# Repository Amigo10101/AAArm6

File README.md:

# AAArm6
robotic arm for a university project

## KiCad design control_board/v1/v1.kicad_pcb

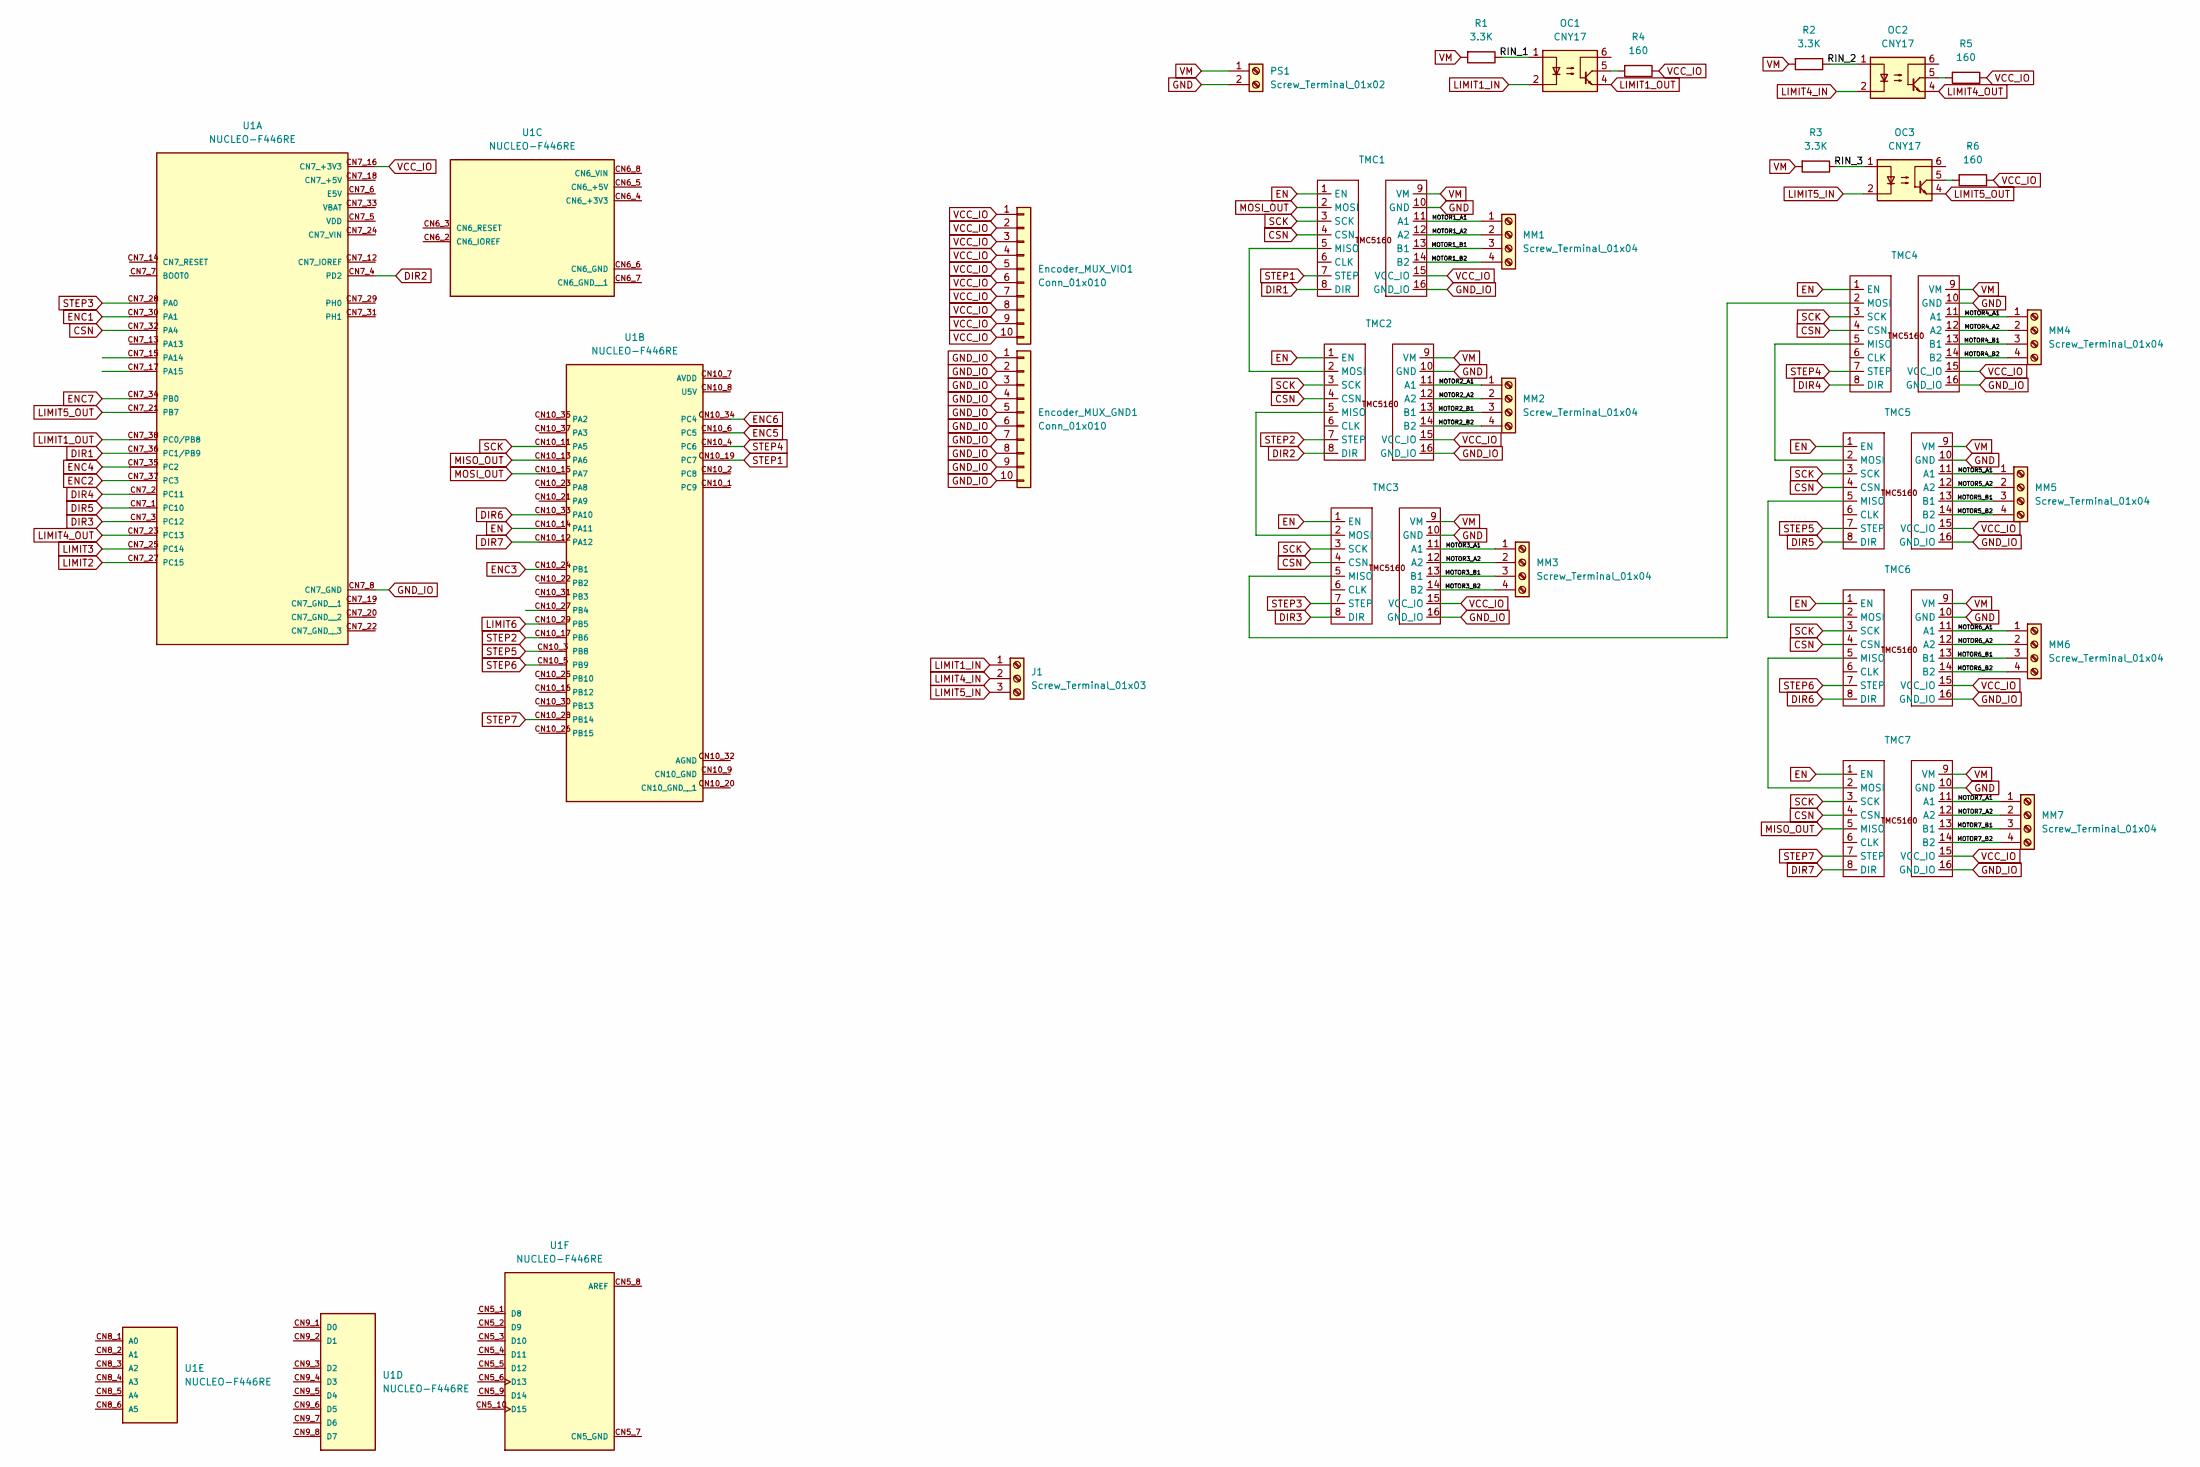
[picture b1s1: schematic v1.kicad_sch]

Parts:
Encoder_MUX_GND1: Conn_01x010; PinSocket_1x10_P2.54mm_Vertical
Encoder_MUX_VIO1: Conn_01x010; PinHeader_1x10_P2.54mm_Vertical
J1: Screw_Terminal_01x03; TerminalBlock_Xinya_XY308-2.54-3P_1x03_P2.54mm_Horizontal
MM1, MM2, MM3, MM4, MM5, MM6, MM7: Screw_Terminal_01x04; TerminalBlock_RND_205-00289_1x04_P5.08mm_Horizontal
OC1, OC2, OC3: CNY17; DIP-6_W7.62mm
PS1: Screw_Terminal_01x02; TerminalBlock_Phoenix_MKDS-3-2-5.08_1x02_P5.08mm_Horizontal
R1, R2, R3: 3.3K; R_Axial_DIN0207_L6.3mm_D2.5mm_P7.62mm_Horizontal
R4, R5, R6: 160; R_Axial_DIN0207_L6.3mm_D2.5mm_P7.62mm_Horizontal
TMC1, TMC2, TMC3, TMC4, TMC5, TMC6, TMC7: tmc5160
U1: NUCLEO-F446RE; MODULE_NUCLEO-F446RE; PARTREV 13

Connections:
/MOTOR1_A1: MM1.1, TMC1.11 (A1)
/MOTOR1_A2: MM1.2, TMC1.12 (A2)
/MOTOR1_B1: MM1.3, TMC1.13 (B1)
/MOTOR1_B2: MM1.4, TMC1.14 (B2)
/MOTOR2_A1: MM2.1, TMC2.11 (A1)
/MOTOR2_A2: MM2.2, TMC2.12 (A2)
/MOTOR2_B1: MM2.3, TMC2.13 (B1)
/MOTOR2_B2: MM2.4, TMC2.14 (B2)
/MOTOR3_A1: MM3.1, TMC3.11 (A1)
/MOTOR3_A2: MM3.2, TMC3.12 (A2)
/MOTOR3_B1: MM3.3, TMC3.13 (B1)
/MOTOR3_B2: MM3.4, TMC3.14 (B2)
/MOTOR4_A1: MM4.1, TMC4.11 (A1)
/MOTOR4_A2: MM4.2, TMC4.12 (A2)
/MOTOR4_B1: MM4.3, TMC4.13 (B1)
/MOTOR4_B2: MM4.4, TMC4.14 (B2)
/MOTOR5_A1: MM5.1, TMC5.11 (A1)
/MOTOR5_A2: MM5.2, TMC5.12 (A2)
/MOTOR5_B1: MM5.3, TMC5.13 (B1)
/MOTOR5_B2: MM5.4, TMC5.14 (B2)
/MOTOR6_A1: MM6.1, TMC6.11 (A1)
/MOTOR6_A2: MM6.2, TMC6.12 (A2)
/MOTOR6_B1: MM6.3, TMC6.13 (B1)
/MOTOR6_B2: MM6.4, TMC6.14 (B2)
/MOTOR7_A1: MM7.1, TMC7.11 (A1)
/MOTOR7_A2: MM7.2, TMC7.12 (A2)
/MOTOR7_B1: MM7.3, TMC7.13 (B1)
/MOTOR7_B2: MM7.4, TMC7.14 (B2)
/RIN_1: OC1.1, R1.1
/RIN_2: OC2.1, R2.1
/RIN_3: OC3.1, R3.1
CSN: TMC1.4 (CSN), TMC2.4 (CSN), TMC3.4 (CSN), TMC4.4 (CSN), TMC5.4 (CSN), TMC6.4 (CSN), TMC7.4 (CSN), U1.CN7_32 (PA4)
DIR1: TMC1.8 (DIR), U1.CN7_36 (PC1/PB9)
DIR2: TMC2.8 (DIR), U1.CN7_4 (PD2)
DIR3: TMC3.8 (DIR), U1.CN7_3 (PC12)
DIR4: TMC4.8 (DIR), U1.CN7_2 (PC11)
DIR5: TMC5.8 (DIR), U1.CN7_1 (PC10)
DIR6: TMC6.8 (DIR), U1.CN10_33 (PA10)
DIR7: TMC7.8 (DIR), U1.CN10_12 (PA12)
EN: TMC1.1 (EN), TMC2.1 (EN), TMC3.1 (EN), TMC4.1 (EN), TMC5.1 (EN), TMC6.1 (EN), TMC7.1 (EN), U1.CN10_14 (PA11)
ENC1: U1.CN7_30 (PA1)
ENC2: U1.CN7_37 (PC3)
ENC3: U1.CN10_24 (PB1)
ENC4: U1.CN7_35 (PC2)
ENC5: U1.CN10_6 (PC5)
ENC6: U1.CN10_34 (PC4)
ENC7: U1.CN7_34 (PB0)
GND: PS1.2, TMC1.10 (GND), TMC2.10 (GND), TMC3.10 (GND), TMC4.10 (GND), TMC5.10 (GND), TMC6.10 (GND), TMC7.10 (GND)
GND_IO: Encoder_MUX_GND1.1, Encoder_MUX_GND1.2, Encoder_MUX_GND1.3, Encoder_MUX_GND1.4, Encoder_MUX_GND1.5, Encoder_MUX_GND1.6, Encoder_MUX_GND1.7, Encoder_MUX_GND1.8, Encoder_MUX_GND1.9, Encoder_MUX_GND1.10, TMC1.16 (GND_IO), TMC2.16 (GND_IO), TMC3.16 (GND_IO), TMC4.16 (GND_IO), TMC5.16 (GND_IO), TMC6.16 (GND_IO), TMC7.16 (GND_IO), U1.CN7_8 (CN7_GND)
LIMIT1_IN: J1.1, OC1.2
LIMIT1_OUT: OC1.4, U1.CN7_38 (PC0/PB8)
LIMIT2: U1.CN7_27 (PC15)
LIMIT3: U1.CN7_25 (PC14)
LIMIT4_IN: J1.2, OC2.2
LIMIT4_OUT: OC2.4, U1.CN7_23 (PC13)
LIMIT5_IN: J1.3, OC3.2
LIMIT5_OUT: OC3.4, U1.CN7_21 (PB7)
LIMIT6: U1.CN10_29 (PB5)
MISO_OUT: TMC7.5 (MISO), U1.CN10_13 (PA6)
MOSI_OUT: TMC1.2 (MOSI), U1.CN10_15 (PA7)
unnamed: OC1.5, R4.2
unnamed: OC2.5, R5.2
unnamed: OC3.5, R6.2
unnamed: TMC1.5 (MISO), TMC2.2 (MOSI)
unnamed: TMC2.5 (MISO), TMC3.2 (MOSI)
unnamed: TMC3.5 (MISO), TMC4.2 (MOSI)
unnamed: TMC4.5 (MISO), TMC5.2 (MOSI)
unnamed: TMC5.5 (MISO), TMC6.2 (MOSI)
unnamed: TMC6.5 (MISO), TMC7.2 (MOSI)
SCK: TMC1.3 (SCK), TMC2.3 (SCK), TMC3.3 (SCK), TMC4.3 (SCK), TMC5.3 (SCK), TMC6.3 (SCK), TMC7.3 (SCK), U1.CN10_11 (PA5)
STEP1: TMC1.7 (STEP), U1.CN10_19 (PC7)
STEP2: TMC2.7 (STEP), U1.CN10_17 (PB6)
STEP3: TMC3.7 (STEP), U1.CN7_28 (PA0)
STEP4: TMC4.7 (STEP), U1.CN10_4 (PC6)
STEP5: TMC5.7 (STEP), U1.CN10_3 (PB8)
STEP6: TMC6.7 (STEP), U1.CN10_5 (PB9)
STEP7: TMC7.7 (STEP), U1.CN10_28 (PB14)
VCC_IO: Encoder_MUX_VIO1.1, Encoder_MUX_VIO1.2, Encoder_MUX_VIO1.3, Encoder_MUX_VIO1.4, Encoder_MUX_VIO1.5, Encoder_MUX_VIO1.6, Encoder_MUX_VIO1.7, Encoder_MUX_VIO1.8, Encoder_MUX_VIO1.9, Encoder_MUX_VIO1.10, R4.1, R5.1, R6.1, TMC1.15 (VCC_IO), TMC2.15 (VCC_IO), TMC3.15 (VCC_IO), TMC4.15 (VCC_IO), TMC5.15 (VCC_IO), TMC6.15 (VCC_IO), TMC7.15 (VCC_IO), U1.CN7_16 (CN7_+3V3)
VM: PS1.1, R1.2, R2.2, R3.2, TMC1.9 (VM), TMC2.9 (VM), TMC3.9 (VM), TMC4.9 (VM), TMC5.9 (VM), TMC6.9 (VM), TMC7.9 (VM)

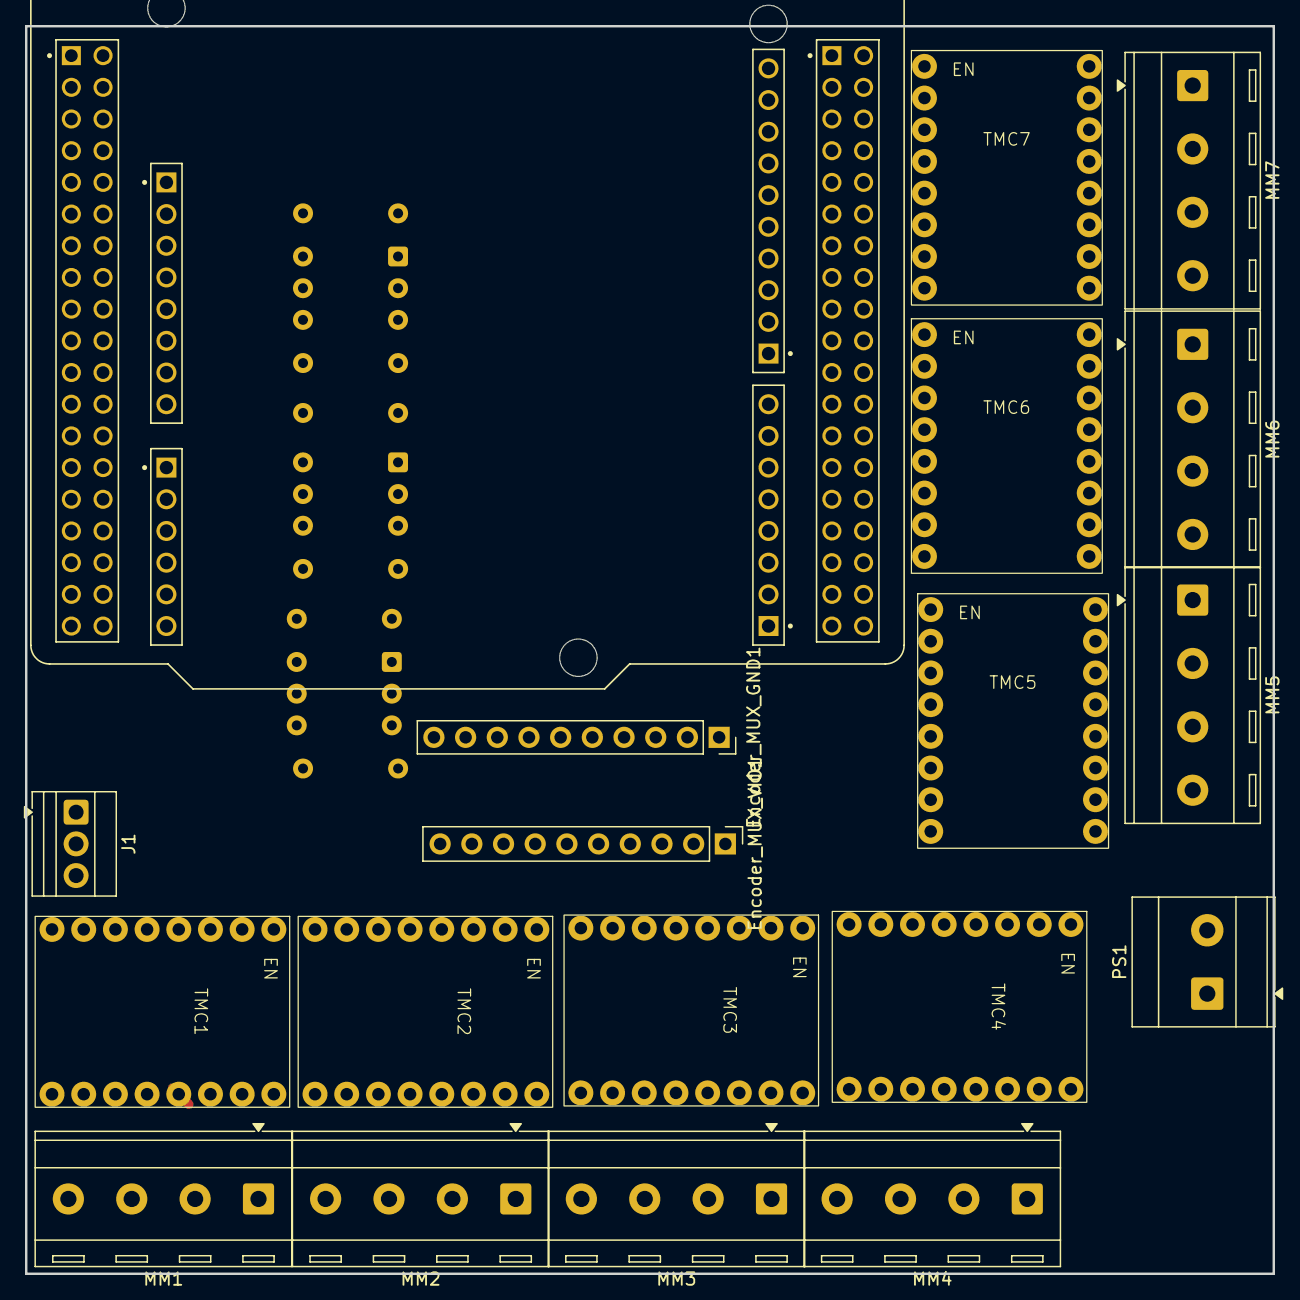
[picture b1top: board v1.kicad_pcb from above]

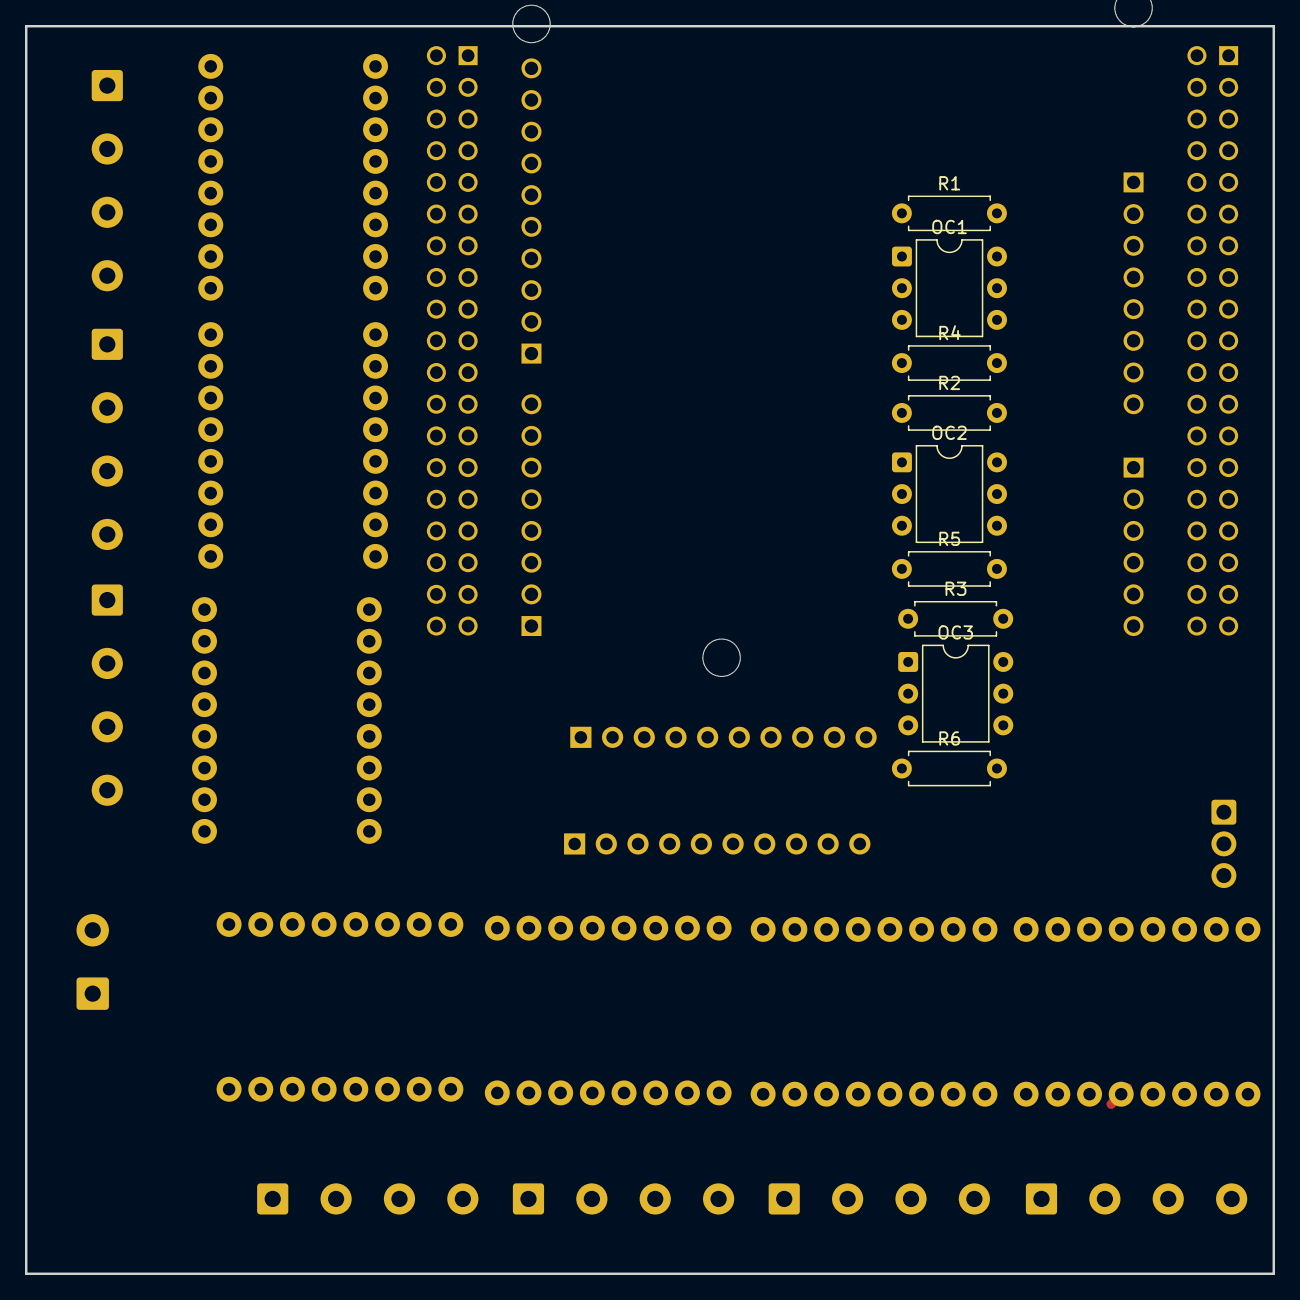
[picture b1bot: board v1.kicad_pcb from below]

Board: 2 copper layers, 100.0 x 100.0 mm, 28 parts (9 on the bottom side), 69 nets.

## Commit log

2025-11-19 working until homing and rviz
2025-11-22 dockerfile part 1 fix
2025-11-25 fix with working in moveit
2025-11-26 fix for better motion and cartesian movements and cleaned up git
2025-11-27 fix with wodden board and cv stuff
